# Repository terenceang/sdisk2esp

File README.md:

# SDISK2 ESP

## An Apple 2 floppy Emulator using ESP32.

This an update the original SDISK2 project by Koichi Nishida (2013).  
It uses it to read the Disk controller signals and return the track data from the disk image.  
A basic UI will be used to select and load an image.

### Todo

1. UI
2. Decode Disk images
3. Disk II emulation.

### Parts

1. ESP32 dev kit 1
2. SSD1306 i2c OLED module.
3. SDcard Module
4. TP223 x 3
5. SN74CB3T3245

Original SDISK II project.
https://tulip-house.ddo.jp/digital/SDISK2/english.html

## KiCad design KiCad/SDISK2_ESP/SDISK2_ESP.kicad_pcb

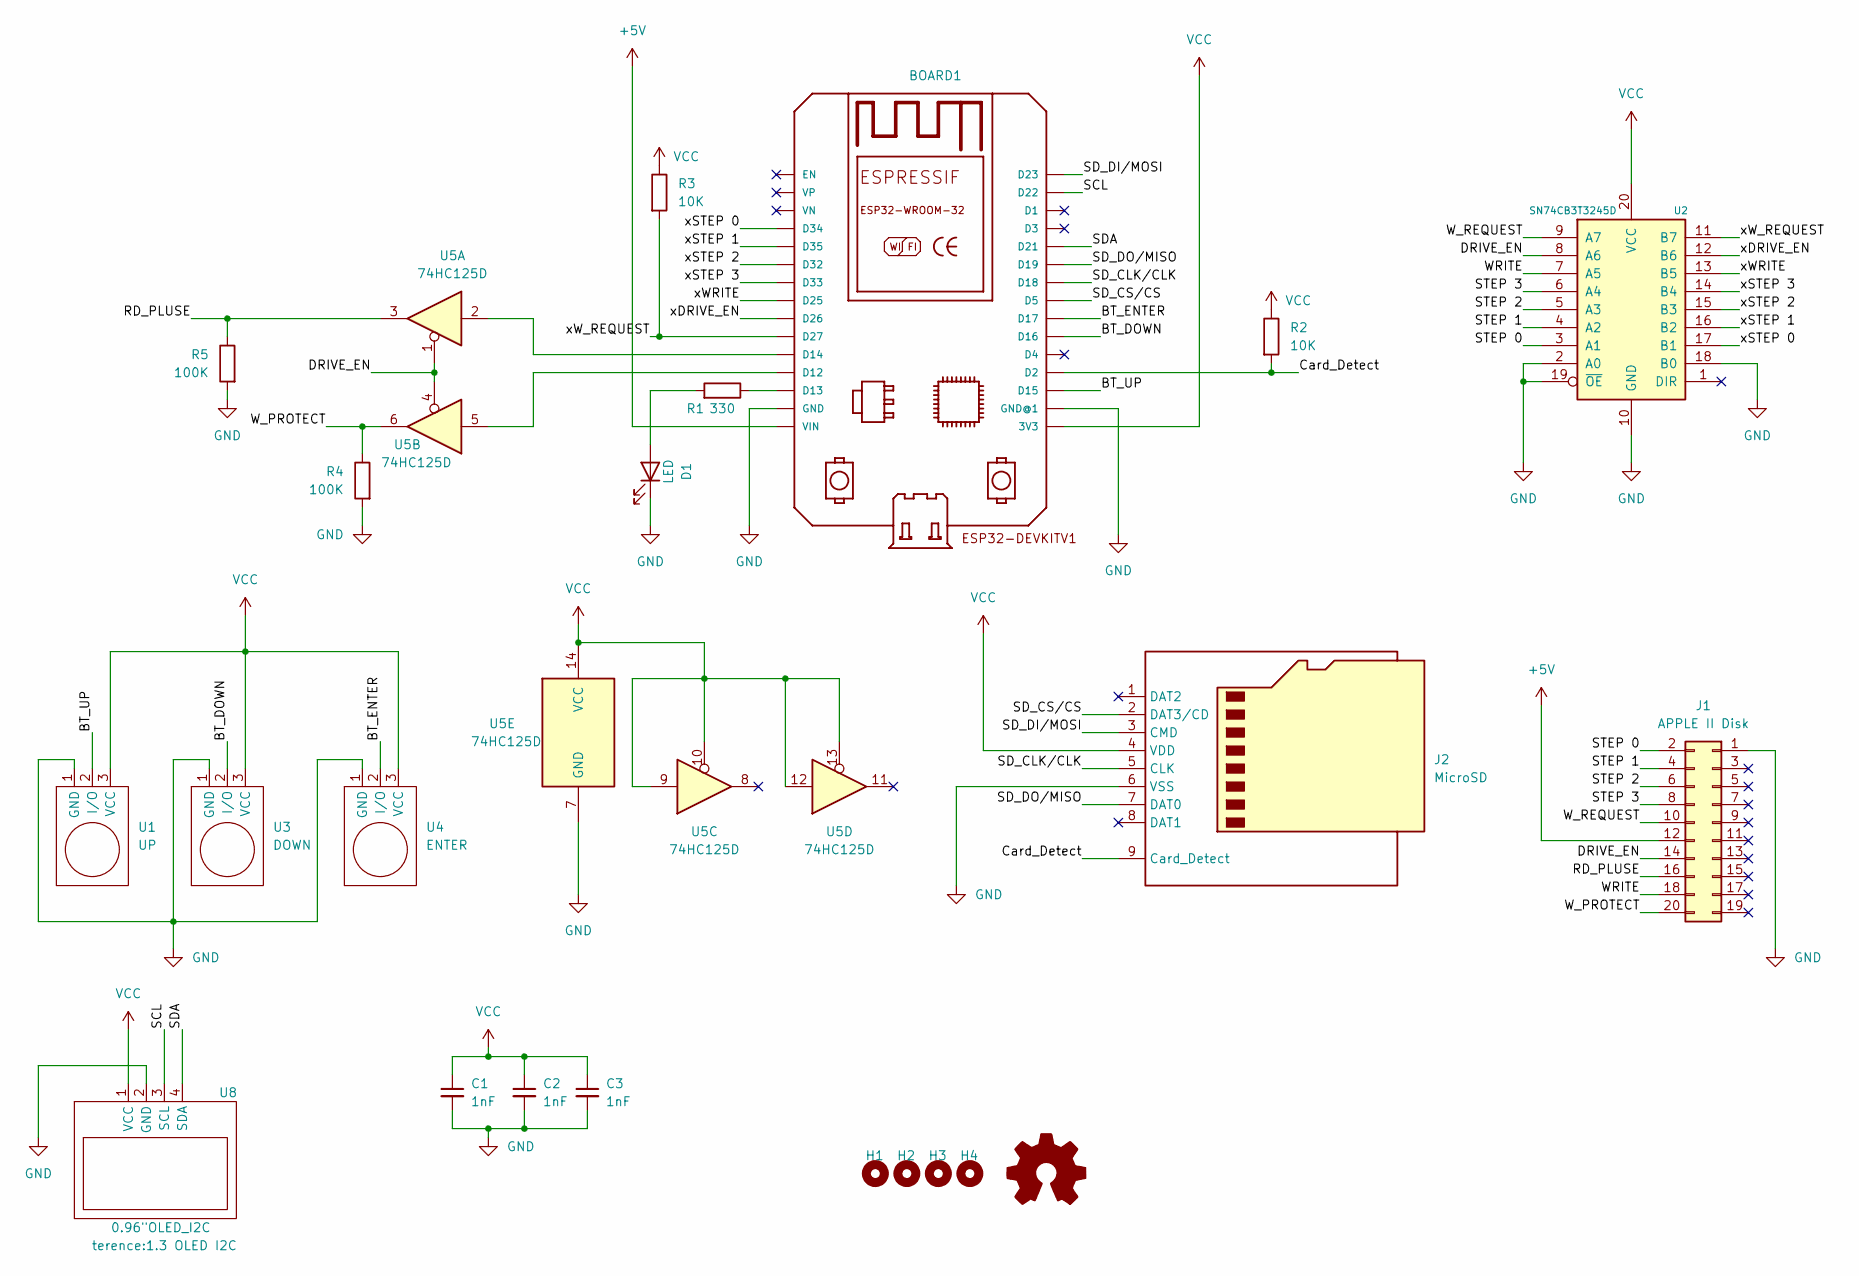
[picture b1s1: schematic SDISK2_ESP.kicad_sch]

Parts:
BOARD1: ESP32DEVKITV1; ESP32-DEVKITV1
C1, C2, C3: 1nF; C_0805_2012Metric
D1: LED; LED_0805_2012Metric
H1, H2, H3, H4: MountingHole; MountingHole_3mm
J1: APPLE II Disk; IDC-Header_2x10_P2.54mm_Horizontal
J2: MicroSD
LOGO1: Logo_Open_Hardware_Small; OSHW-Symbol_6.7x6mm_SilkScreen
R1: 330; R_0805_2012Metric
R2, R3: 10K; R_0805_2012Metric
R4, R5: 100K; R_0805_2012Metric
U1: UP; TP223
U2: SN74CB3T3245D; SOIC-20W_7.5x12.8mm_P1.27mm
U3: DOWN; TP223
U4: ENTER; TP223
U5: 74HC125D; SOIC-14_3.9x8.7mm_P1.27mm
U8: 0.96"OLED_I2C; 1.3 OLED I2C

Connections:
+5V: BOARD1.VIN, J1.12
/BT_DOWN: BOARD1.D16, U3.2 (I/O)
/BT_ENTER: BOARD1.D17, U4.2 (I/O)
/BT_UP: BOARD1.D15, U1.2 (I/O)
/Card_Detect: BOARD1.D2, J2.9 (Card_Detect), R2.2
/DRIVE_EN: J1.14, U2.8 (A6), U5.1, U5.4
/RD_PLUSE: J1.16, R5.1, U5.3
/SCL: BOARD1.D22, U8.3 (SCL); also elsewhere on the board
/SDA: BOARD1.D21, U8.4 (SDA); also elsewhere on the board
/SD_CLK/CLK: BOARD1.D18, J2.5 (CLK)
/SD_CS/CS: BOARD1.D5, J2.2 (DAT3/CD)
/SD_DI/MOSI: BOARD1.D23, J2.3 (CMD)
/SD_DO/MISO: BOARD1.D19, J2.7 (DAT0)
/STEP 0: J1.2, U2.3 (A1)
/STEP 1: J1.4, U2.4 (A2)
/STEP 2: J1.6, U2.5 (A3)
/STEP 3: J1.8, U2.6 (A4)
/WRITE: J1.18, U2.7 (A5)
/W_PROTECT: J1.20, R4.1, U5.6
/W_REQUEST: J1.10, U2.9 (A7)
/xDRIVE_EN: BOARD1.D26, U2.12 (B6)
/xSTEP 0: BOARD1.D34, U2.17 (B1)
/xSTEP 1: BOARD1.D35, U2.16 (B2)
/xSTEP 2: BOARD1.D32, U2.15 (B3)
/xSTEP 3: BOARD1.D33, U2.14 (B4)
/xWRITE: BOARD1.D25, U2.13 (B5)
/xW_REQUEST: BOARD1.D27, R3.2, U2.11 (B7)
GND: BOARD1.GND, BOARD1.GND@1, C1.2, C2.2, C3.2, D1.1 (K), J1.1, J2.6 (VSS), R4.2, R5.2, U1.1 (GND), U2.2 (A0), U2.10 (GND), U2.18 (B0), U2.19 (~OE), U3.1 (GND), U4.1 (GND), U5.7 (GND), U8.2 (GND); also elsewhere on the board
unnamed: BOARD1.D12, U5.5
unnamed: BOARD1.D13, R1.1
unnamed: BOARD1.D14, U5.2
unnamed: D1.2 (A), R1.2
VCC: BOARD1.3V3, C1.1, C2.1, C3.1, J2.4 (VDD), R2.1, R3.1, U1.3 (VCC), U2.20 (VCC), U3.3 (VCC), U4.3 (VCC), U5.9, U5.10, U5.12, U5.13, U5.14 (VCC), U8.1 (VCC); also elsewhere on the board

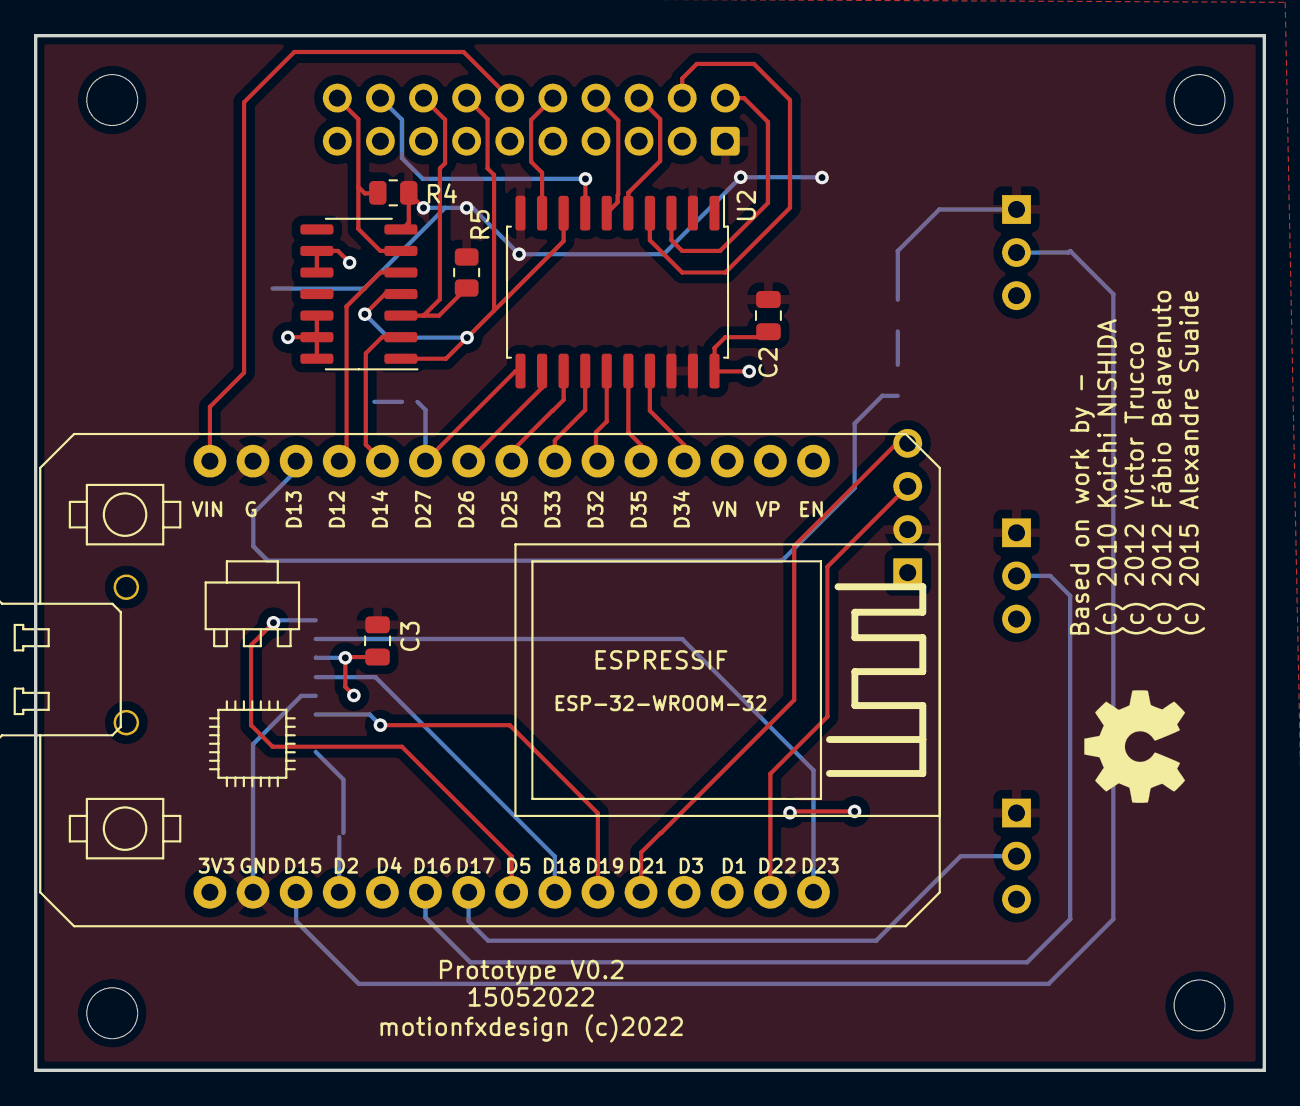
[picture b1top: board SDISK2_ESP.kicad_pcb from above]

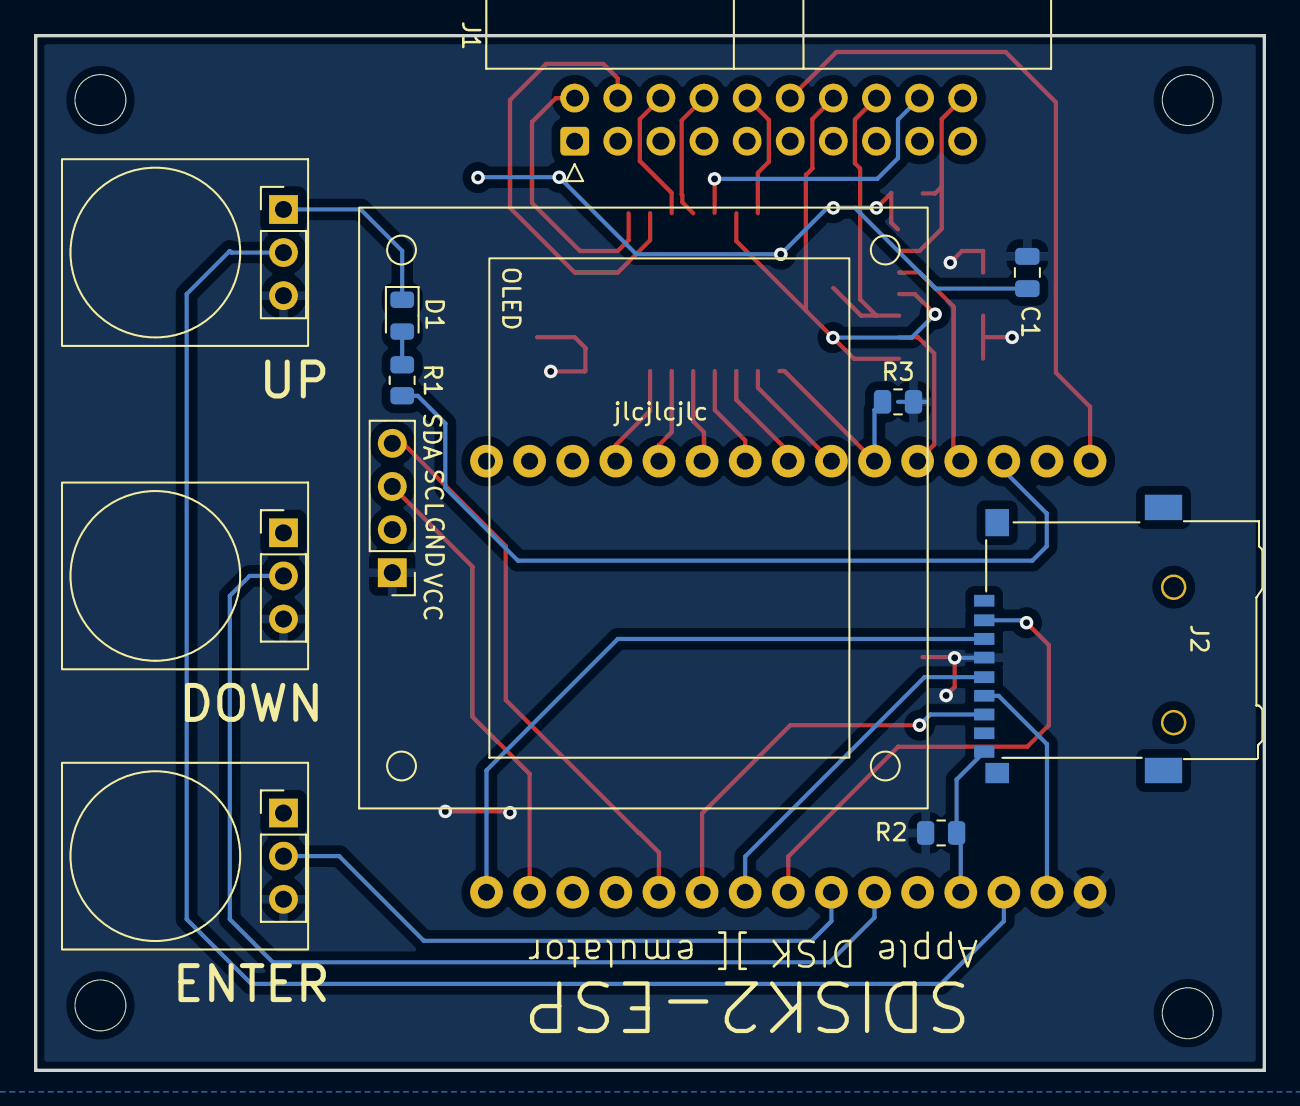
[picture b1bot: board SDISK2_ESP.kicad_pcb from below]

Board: 2 copper layers, 72.4 x 61.0 mm, 23 parts (11 on the bottom side), 33 nets.

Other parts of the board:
OLED: 0.96"OLED_I2C; 1.3 OLED I2C

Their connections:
/SCL: OLED.3 (SCL); also elsewhere on the board
/SDA: OLED.4 (SDA); also elsewhere on the board
GND: OLED.2 (GND); also elsewhere on the board
VCC: OLED.1 (VCC); also elsewhere on the board

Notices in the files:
KiCad/SDISK2_ESP/SDISK2_ESP.kicad_pcb:
motionfxdesign (c)2022
(c) 2010 Koichi NISHIDA
(c) 2012 Victor Trucco
(c) 2012 Fábio Belavenuto
(c) 2015 Alexandre Suaide
